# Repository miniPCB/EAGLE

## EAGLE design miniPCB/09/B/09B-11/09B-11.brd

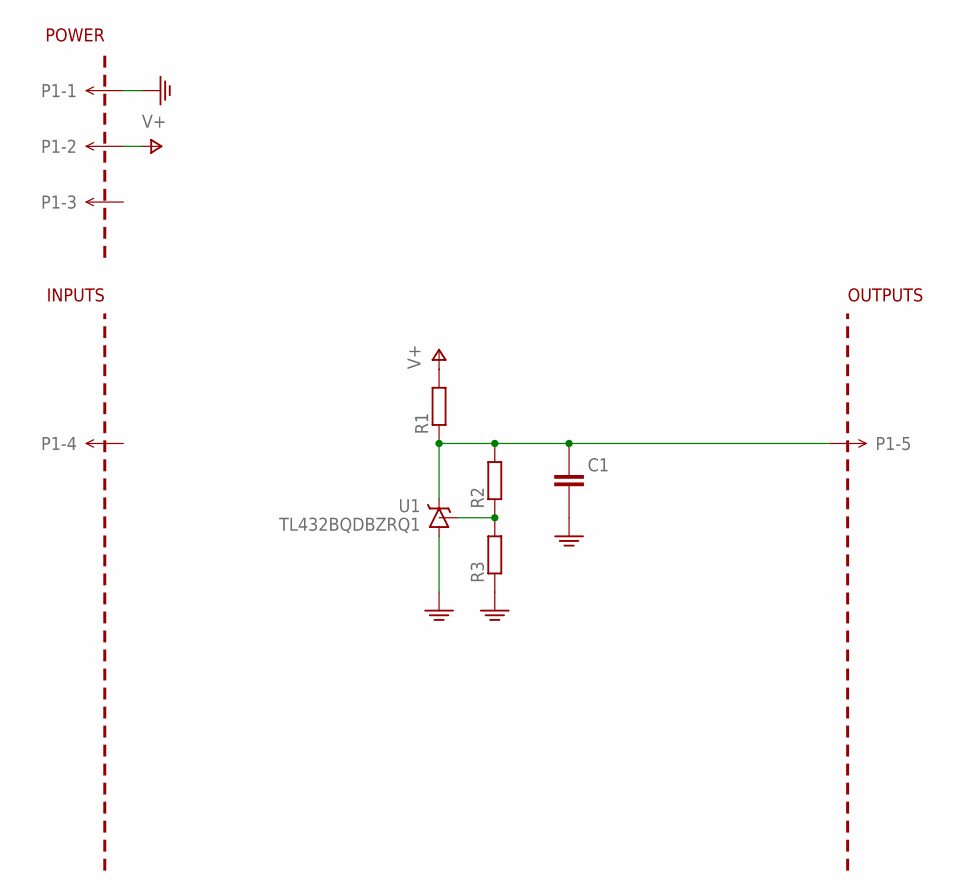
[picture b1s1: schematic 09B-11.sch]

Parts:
C1: CAPACITORSMD; C0805
P1: MINIPCB_5P5P; PINS_1X5
PCB1: MINIPCB_0PPCB20-20; PCB20-20; PART_NUMBER 09B-11
R1, R2, R3: RESISTORSMD; R0805
U1: TL432BQDBZRQ1; SOT95P237X112-3N

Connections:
GND: C1.2ASDF (-), P1.1, R3.1, U1.3 (A)
unnamed: C1.1ASD (+), P1.5, R1.1, R2.2, U1.1 (C)
unnamed: R2.1, R3.2, U1.2 (REF)
V+: P1.2, R1.2

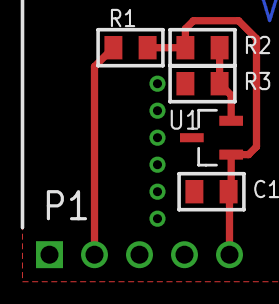
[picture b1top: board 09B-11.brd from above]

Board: 2 copper layers, 7 parts (0 on the bottom side), 4 nets.

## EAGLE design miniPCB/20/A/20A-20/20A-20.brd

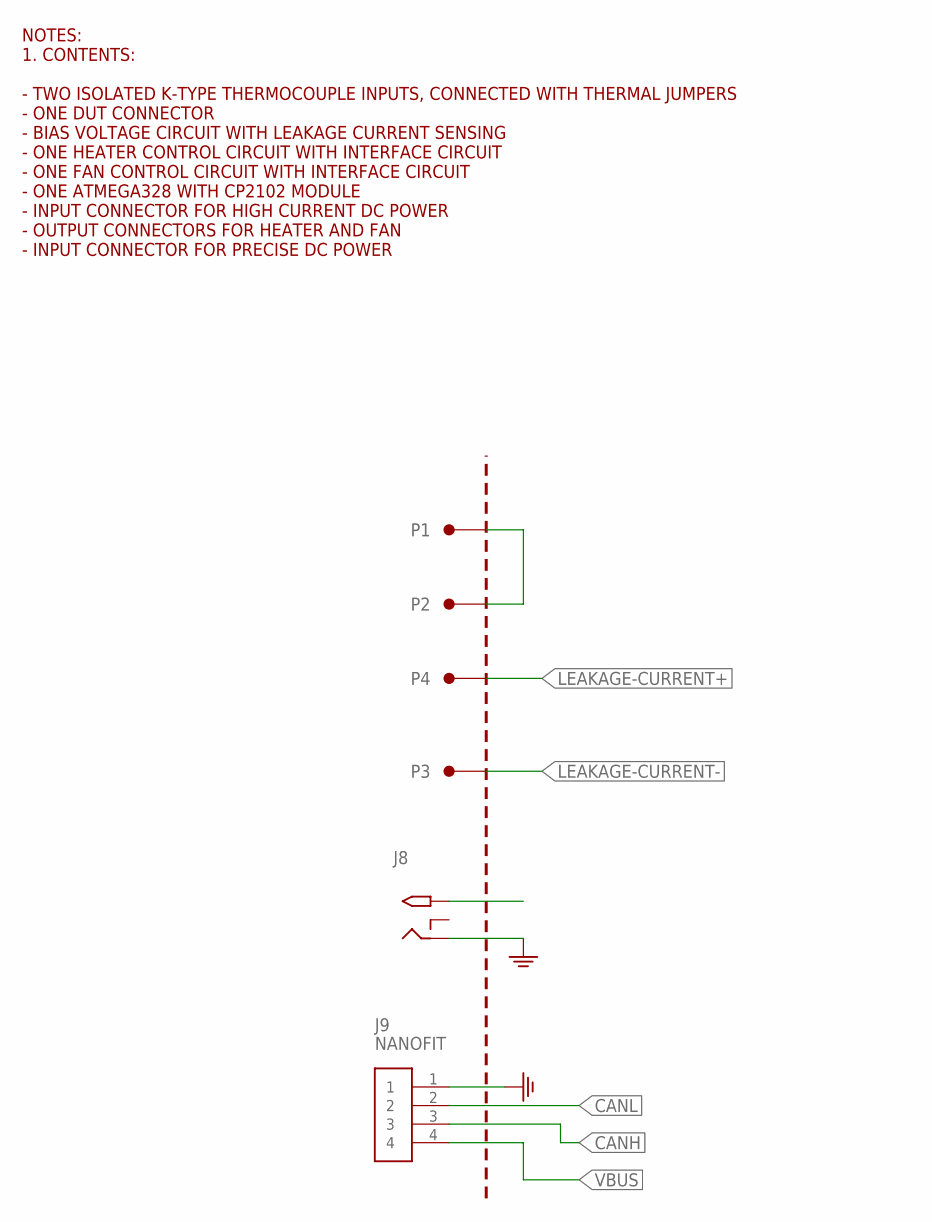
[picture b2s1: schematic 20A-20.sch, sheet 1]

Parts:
J8: 2.1MMJACKTHM; PJ-102A
J9: NANOFIT; PINS_4_NANOFIT_RA
P1, P2, P3, P4: PINS_1571-0500; BANNAN_JACK_4MM_H
PCB1: MINIPCB_0P100X100; MINIPCB_DOCK_100X100; PART_NUMBER 20A-20

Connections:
CANH: J9.3; also elsewhere on the board
CANL: J9.2; also elsewhere on the board
GND: J8.RING, J9.1; also elsewhere on the board
LEAKAGE-CURRENT+: P4.1, P4.2; also elsewhere on the board
LEAKAGE-CURRENT-: P3.1, P3.2; also elsewhere on the board
unnamed: P1.1, P1.2, P2.1, P2.2
VBUS: J9.4

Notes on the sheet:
NOTES: 1. CONTENTS: - TWO ISOLATED K-TYPE THERMOCOUPLE INPUTS, CONNECTED WITH THERMAL JUMPERS - ONE DUT CONNECTOR - BIAS VOLTAGE CIRCUIT WITH LEAKAGE CURRENT SENSING - ONE HEATER CONTROL CIRCUIT WITH INTERFACE CIRCUIT - ONE FAN CONTROL CIRCUIT WITH INTERFACE CIRCUIT - ONE ATMEGA328 WITH CP2102 MODU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

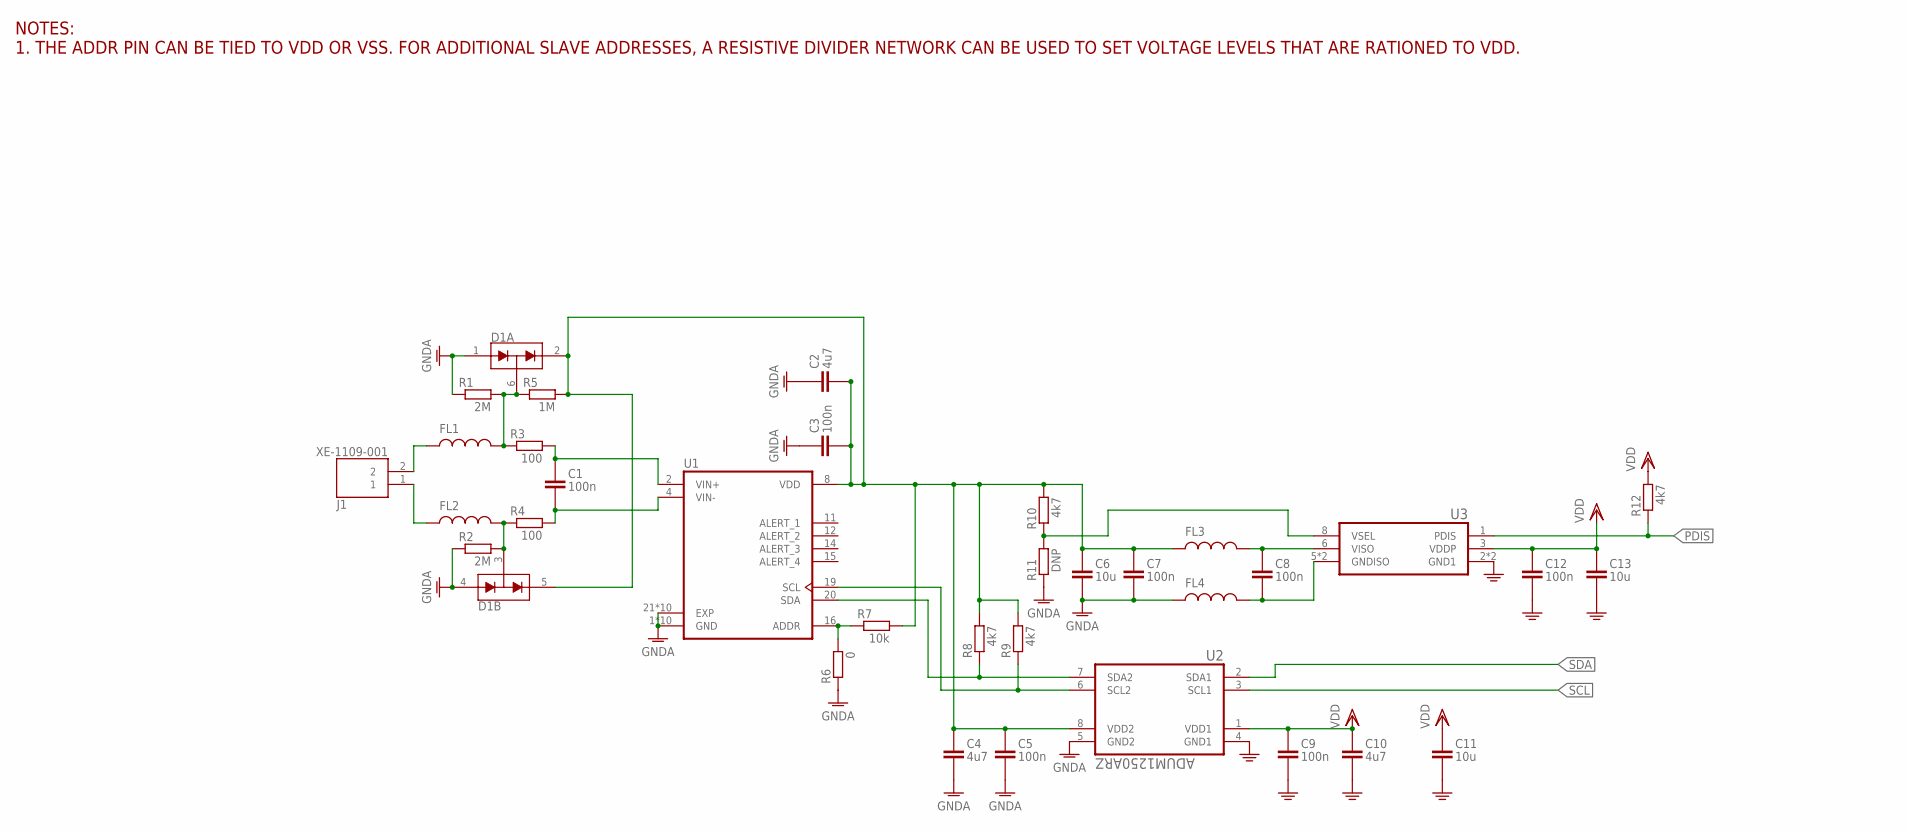
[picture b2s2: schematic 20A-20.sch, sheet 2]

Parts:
C1, C3, C5, C7, C8, C9, C12: 100n; C0402
C2, C4, C10: 4u7; C0402
C6, C11, C13: 10u; C0805
D1: SDA004-7; SOT363
FL1, FL2, FL3, FL4: BLM03HG601SZ1D; R0402
J1: XE-1109-001
R1, R2: 2M; R0402
R3, R4: 100; R0402
R5: 1M; R0402
R6: 0; R0402
R7: 10k; R0402
R8, R9, R10, R12: 4k7; R0402
R11: DNP; R0402
U1: MCP9600T-I/MX; QFN65P500X500X100-21N_MCP9600T-I/MX
U2: ADUM1250ARZ; SOIC127P600X175-8N
U3: ADUM6280; SOIC127P600X175-8N

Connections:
GND: C9.2 (-), C10.2 (-), C11.2ASDF (-), C12.2 (-), C13.2ASDF (-), U2.4 (GND1), U3.2 (GND1), U3.4 (GND1); also elsewhere on the board
GNDA: C2.1 (+), C3.1 (+), C4.2 (-), C5.2 (-), C6.2ASDF (-), C7.2 (-), D1.1 (A1), D1.4 (A1), FL4.1, R1.1, R2.1, R6.1, R11.1, U1.1 (GND), U1.3 (GND), U1.5 (GND), U1.6 (GND), U1.7 (GND), U1.9 (GND), U1.10 (GND), U1.13 (GND), U1.17 (GND), U1.18 (GND), U1.21 (EXP), U1.22 (EXP), U1.23 (EXP), U1.24 (EXP), U1.25 (EXP), U1.26 (EXP), U1.27 (EXP), U1.28 (EXP), U1.29 (EXP), U1.30 (EXP), U2.5 (GND2); also elsewhere on the board
unnamed: D1.6 (COM), FL1.2, R1.2, R3.1, R5.1
unnamed: R9.1, U1.19 (SCL), U2.6 (SCL2)
unnamed: R8.1, U1.20 (SDA), U2.7 (SDA2)
unnamed: C8.2 (-), FL4.2, U3.5 (GNDISO), U3.7 (GNDISO)
unnamed: C8.1 (+), FL3.2, U3.6 (VISO)
unnamed: R10.1, R11.2, U3.8 (VSEL)
unnamed: R6.2, R7.1, U1.16 (ADDR)
unnamed: C1.1 (+), R3.2, U1.2 (VIN+)
unnamed: D1.3 (COM), FL2.2, R2.2, R4.1
unnamed: C1.2 (-), R4.2, U1.4 (VIN-)
unnamed: FL1.1, J1.2
unnamed: FL2.1, J1.1
PDIS: R12.1, U3.1 (PDIS); also elsewhere on the board
SCL: U2.3 (SCL1); also elsewhere on the board
SDA: U2.2 (SDA1); also elsewhere on the board
VDD: C9.1 (+), C10.1 (+), C11.1ASD (+), C12.1 (+), C13.1ASD (+), R12.2, U2.1 (VDD1), U3.3 (VDDP); also elsewhere on the board
VISO: C2.2 (-), C3.2 (-), C4.1 (+), C5.1 (+), C6.1ASD (+), C7.1 (+), D1.2 (C2), D1.5 (C2), FL3.1, R5.2, R7.2, R8.2, R9.2, R10.2, U1.8 (VDD), U2.8 (VDD2)

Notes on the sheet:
NOTES: 1. THE ADDR PIN CAN BE TIED TO VDD OR VSS. FOR ADDITIONAL SLAVE ADDRESSES, A RESISTIVE DIVIDER NETWORK CAN BE USED TO SET VOLTAGE LEVELS THAT ARE RATIONED TO VDD.

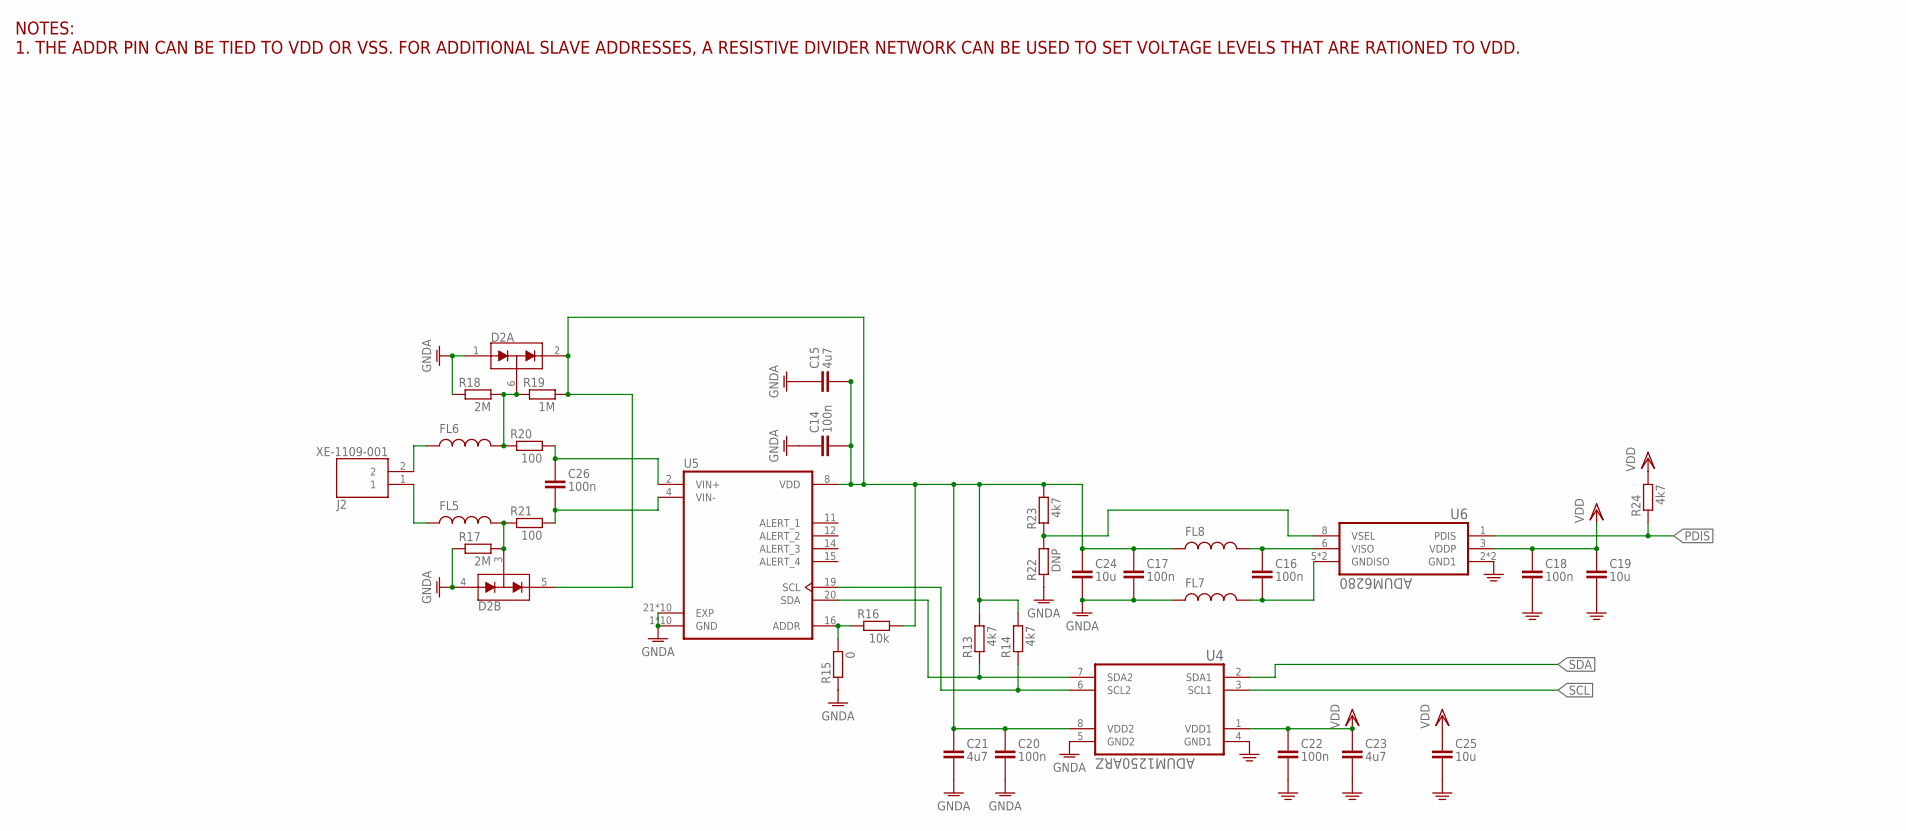
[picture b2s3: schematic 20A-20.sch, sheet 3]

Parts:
C14, C16, C17, C18, C20, C22, C26: 100n; C0402
C15, C21, C23: 4u7; C0402
C19, C24, C25: 10u; C0805
D2: SDA004-7; SOT363
FL5, FL6, FL7, FL8: BLM03HG601SZ1D; R0402
J2: XE-1109-001
R13, R14, R23, R24: 4k7; R0402
R15: 0; R0402
R16: 10k; R0402
R17, R18: 2M; R0402
R19: 1M; R0402
R20, R21: 100; R0402
R22: DNP; R0402
U4: ADUM1250ARZ; SOIC127P600X175-8N
U5: MCP9600T-I/MX; QFN65P500X500X100-21N_MCP9600T-I/MX
U6: ADUM6280; SOIC127P600X175-8N

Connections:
GND: C18.2 (-), C19.2ASDF (-), C22.2 (-), C23.2 (-), C25.2ASDF (-), U4.4 (GND1), U6.2 (GND1), U6.4 (GND1); also elsewhere on the board
GNDA: C14.1 (+), C15.1 (+), C17.2 (-), C20.2 (-), C21.2 (-), C24.2ASDF (-), D2.1 (A1), D2.4 (A1), FL7.1, R15.1, R17.1, R18.1, R22.1, U4.5 (GND2), U5.1 (GND), U5.3 (GND), U5.5 (GND), U5.6 (GND), U5.7 (GND), U5.9 (GND), U5.10 (GND), U5.13 (GND), U5.17 (GND), U5.18 (GND), U5.21 (EXP), U5.22 (EXP), U5.23 (EXP), U5.24 (EXP), U5.25 (EXP), U5.26 (EXP), U5.27 (EXP), U5.28 (EXP), U5.29 (EXP), U5.30 (EXP); also elsewhere on the board
unnamed: R14.1, U4.6 (SCL2), U5.19 (SCL)
unnamed: R13.1, U4.7 (SDA2), U5.20 (SDA)
unnamed: R15.2, R16.1, U5.16 (ADDR)
unnamed: D2.6 (COM), FL6.2, R18.2, R19.1, R20.1
unnamed: D2.3 (COM), FL5.2, R17.2, R21.1
unnamed: C26.1 (+), R20.2, U5.2 (VIN+)
unnamed: C26.2 (-), R21.2, U5.4 (VIN-)
unnamed: FL6.1, J2.2
unnamed: FL5.1, J2.1
unnamed: R22.2, R23.1, U6.8 (VSEL)
unnamed: C16.2 (-), FL7.2, U6.5 (GNDISO), U6.7 (GNDISO)
unnamed: C16.1 (+), FL8.2, U6.6 (VISO)
PDIS: R24.1, U6.1 (PDIS); also elsewhere on the board
SCL: U4.3 (SCL1); also elsewhere on the board
SDA: U4.2 (SDA1); also elsewhere on the board
VDD: C18.1 (+), C19.1ASD (+), C22.1 (+), C23.1 (+), C25.1ASD (+), R24.2, U4.1 (VDD1), U6.3 (VDDP); also elsewhere on the board
VISO1: C14.2 (-), C15.2 (-), C17.1 (+), C20.1 (+), C21.1 (+), C24.1ASD (+), D2.2 (C2), D2.5 (C2), FL8.1, R13.2, R14.2, R16.2, R19.2, R23.2, U4.8 (VDD2), U5.8 (VDD)

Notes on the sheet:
NOTES: 1. THE ADDR PIN CAN BE TIED TO VDD OR VSS. FOR ADDITIONAL SLAVE ADDRESSES, A RESISTIVE DIVIDER NETWORK CAN BE USED TO SET VOLTAGE LEVELS THAT ARE RATIONED TO VDD.

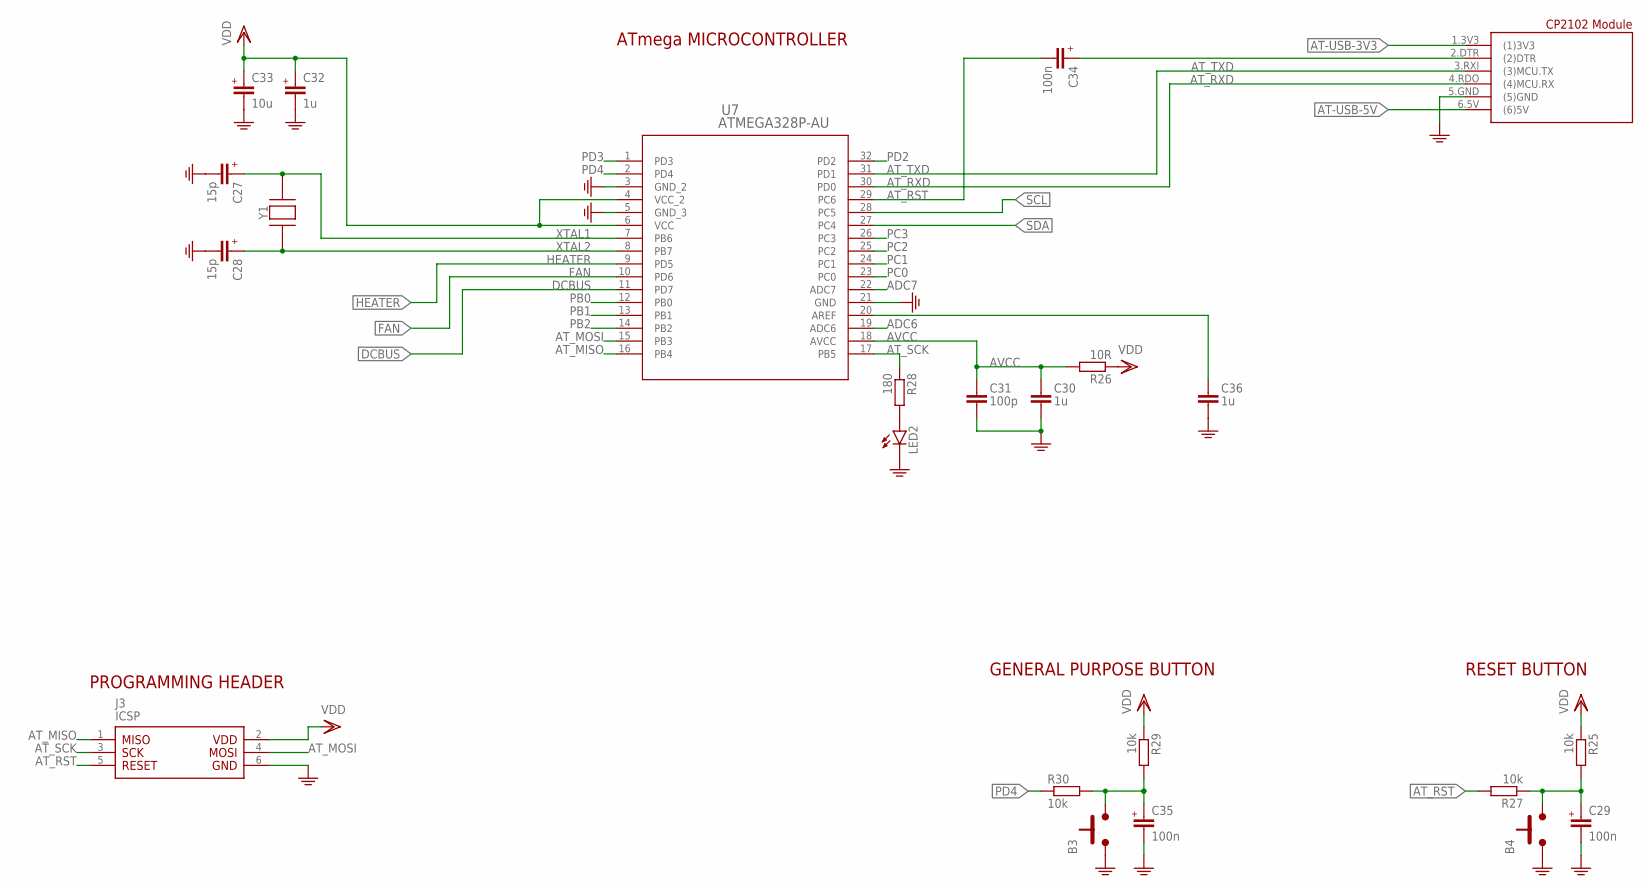
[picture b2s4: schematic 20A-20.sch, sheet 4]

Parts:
B3, B4: PUSHBUTTON6X6MM; 6X6MM
C27, C28: 15p; C0603
C29, C34, C35: 100n; C0805
C30, C32, C36: 1u; C0805
C31: 100p; C0805
C33: 10u; C0805
J3: ICSP; PINS_6-2X3_AT
LED2: LEDSML0805; SML0805
R25, R27, R29, R30: 10k; R0805
R26: 10R; R0805
R28: 180; R0805
U7: ATMEGA328P-AU; 32A_ATM
U8: VIVA_USB-TTL; VIVA_USB_TTL_SUBTEXT
Y1: CRYSTAL-3225_4P; TXC7M2

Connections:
ADC6: U7.19 (ADC6)
ADC7: U7.22 (ADC7)
AT-USB-3V3: U8.1.3V3 ((1)3V3)
AT-USB-5V: U8.6.5V ((6)5V)
AT_DTR_CAP: C34.1 (+), U8.2.DTR ((2)DTR)
AT_MISO: J3.1, U7.16 (PB4)
AT_MOSI: J3.4, U7.15 (PB3)
AT_RST: C34.2 (-), J3.5, R27.2, U7.29 (PC6)
AT_RST_CAP: B4.3.B (2), B4.4.B (2), C29.1 (+), R25.2, R27.1
AT_RXD: U7.30 (PD0), U8.4.RDO ((4)MCU.RX)
AT_SCK: J3.3, R28.1, U7.17 (PB5)
AT_TXD: U7.31 (PD1), U8.3.RXI ((3)MCU.TX)
AVCC: C30.1, C31.1, R26.2, U7.18 (AVCC)
DCBUS: U7.11 (PD7); also elsewhere on the board
FAN: U7.10 (PD6); also elsewhere on the board
GND: B3.1.A (1), B3.2.A (1), B4.1.A (1), B4.2.A (1), C27.1 (-), C28.1 (-), C29.2 (-), C30.2, C31.2, C32.2 (-), C33.2 (-), C35.2 (-), C36.2, J3.6, LED2.C, U7.3 (GND_2), U7.5 (GND_3), U7.21 (GND), U8.5.GND ((5)GND); also elsewhere on the board
HEATER: U7.9 (PD5); also elsewhere on the board
unnamed: C36.1, U7.20 (AREF)
unnamed: LED2.A, R28.2
PB0: U7.12 (PB0)
PB1: U7.13 (PB1)
PB2: U7.14 (PB2)
PC0: U7.23 (PC0)
PC1: U7.24 (PC1)
PC2: U7.25 (PC2)
PC3: U7.26 (PC3)
PD2: U7.32 (PD2)
PD3: U7.1 (PD3)
PD4: R30.1, U7.2 (PD4)
PD4-CAP: B3.3.B (2), B3.4.B (2), C35.1 (+), R29.2, R30.2
SCL: U7.28 (PC5); also elsewhere on the board
SDA: U7.27 (PC4); also elsewhere on the board
VDD: C32.1 (+), C33.1 (+), J3.2, R25.1, R26.1, R29.1, U7.4 (VCC_2), U7.6 (VCC); also elsewhere on the board
XTAL1: C27.2 (+), U7.7 (PB6), Y1.3 (2)
XTAL2: C28.2 (+), U7.8 (PB7), Y1.1

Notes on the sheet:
PROGRAMMING HEADER
ATmega MICROCONTROLLER
RESET BUTTON
GENERAL PURPOSE BUTTON

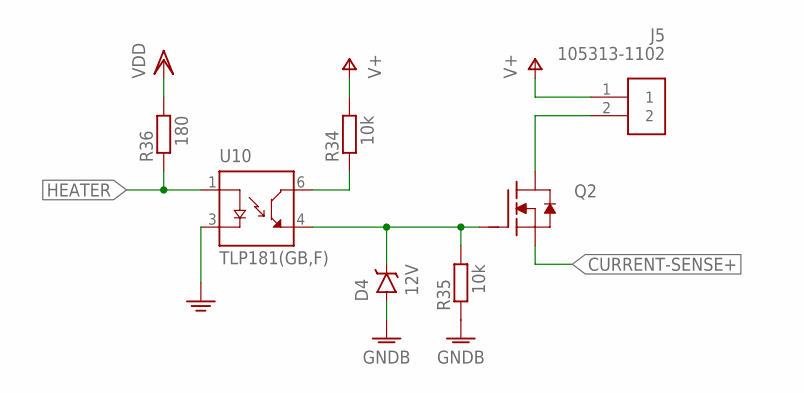
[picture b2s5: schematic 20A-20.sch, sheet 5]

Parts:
D4: 12V; SOT23
J5: 105313-1102; PINS_2-NANOFIT-H
Q2: MOSFET-NDPAK; DPACK
R34, R35: 10k; R0805
R36: 180; R0805
U10: TLP181(GB,F); SOIC254P700X280-4N

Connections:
CURRENT-SENSE+: Q2.3 (S); also elsewhere on the board
GND: U10.3 (C); also elsewhere on the board
GNDB: D4.1 (A), R35.1; also elsewhere on the board
HEATER: R36.1, U10.1 (A); also elsewhere on the board
unnamed: D4.3 (C), Q2.1 (G), R35.2, U10.4 (ET)
unnamed: J5.2, Q2.4 (D)
unnamed: R34.1, U10.6 (CT)
V+: J5.1, R34.2; also elsewhere on the board
VDD: R36.2; also elsewhere on the board

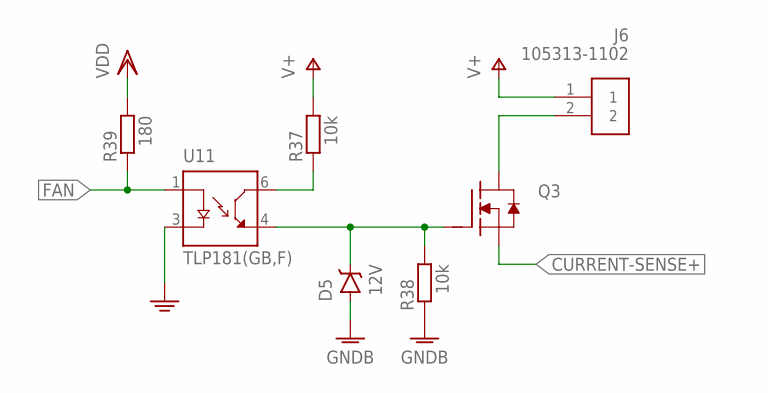
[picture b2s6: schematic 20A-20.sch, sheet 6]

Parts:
D5: 12V; SOT23
J6: 105313-1102; PINS_2-NANOFIT-H
Q3: MOSFET-NDPAK; DPACK
R37, R38: 10k; R0805
R39: 180; R0805
U11: TLP181(GB,F); SOIC254P700X280-4N

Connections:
CURRENT-SENSE+: Q3.3 (S); also elsewhere on the board
FAN: R39.1, U11.1 (A); also elsewhere on the board
GND: U11.3 (C); also elsewhere on the board
GNDB: D5.1 (A), R38.1; also elsewhere on the board
unnamed: D5.3 (C), Q3.1 (G), R38.2, U11.4 (ET)
unnamed: J6.2, Q3.4 (D)
unnamed: R37.1, U11.6 (CT)
V+: J6.1, R37.2; also elsewhere on the board
VDD: R39.2; also elsewhere on the board

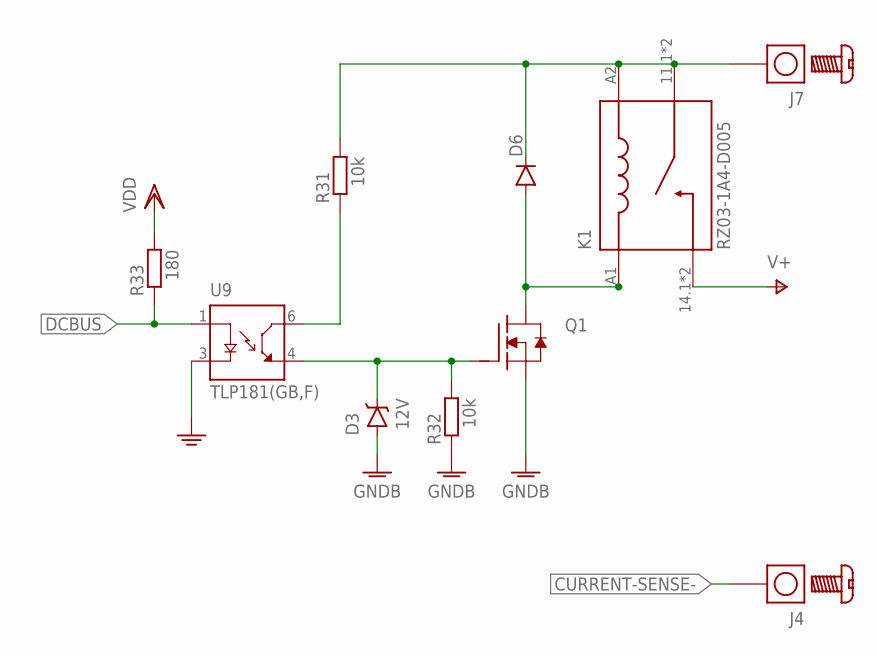
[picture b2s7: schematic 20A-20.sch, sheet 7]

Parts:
D3: 12V; SOT23
D6: DIODE-SOD323-W; SOD323-W
J4, J7: SCREW-TERMINAL; SCREW-TERMINAL-M3
K1: RZ03-1A4-D005; RELAY_RZ03-1A4-D005
Q1: MOSFET-NSOT23; SOT23
R31, R32: 10k; R0805
R33: 180; R0805
U9: TLP181(GB,F); SOIC254P700X280-4N

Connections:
CURRENT-SENSE-: J4.1, J4.2, J4.3, J4.4; also elsewhere on the board
DCBUS: R33.1, U9.1 (A); also elsewhere on the board
GND: U9.3 (C); also elsewhere on the board
GNDB: D3.1 (A), Q1.2 (S), R32.1; also elsewhere on the board
unnamed: D3.3 (C), Q1.1 (G), R32.2, U9.4 (ET)
unnamed: D6.C, J7.1, J7.2, J7.3, J7.4, K1.11.1 (11), K1.11.2 (11), K1.A2, R31.2
unnamed: D6.A, K1.A1, Q1.3 (D)
unnamed: R31.1, U9.6 (CT)
V+: K1.14.1 (14), K1.14.2 (14); also elsewhere on the board
VDD: R33.2; also elsewhere on the board

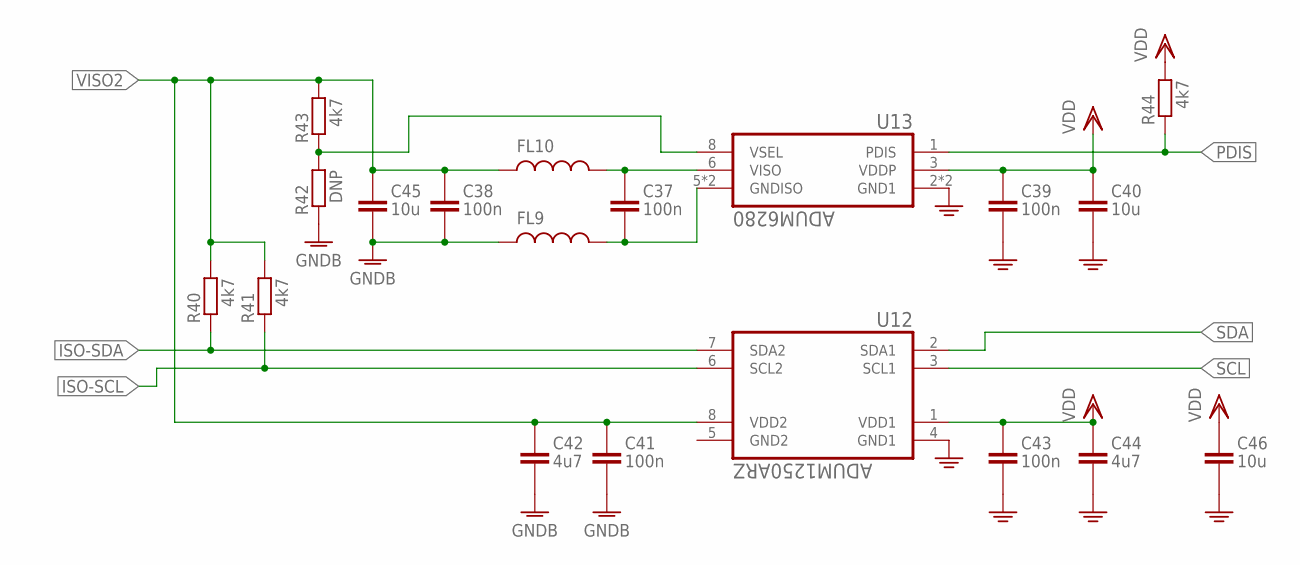
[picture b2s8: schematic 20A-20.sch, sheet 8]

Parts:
C37, C38, C39, C41, C43: 100n; C0402
C40, C45, C46: 10u; C0805
C42, C44: 4u7; C0402
FL9, FL10: BLM03HG601SZ1D; R0402
R40, R41, R43, R44: 4k7; R0402
R42: DNP; R0402
U12: ADUM1250ARZ; SOIC127P600X175-8N
U13: ADUM6280; SOIC127P600X175-8N

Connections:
GND: C39.2 (-), C40.2ASDF (-), C43.2 (-), C44.2 (-), C46.2ASDF (-), U12.4 (GND1), U13.2 (GND1), U13.4 (GND1); also elsewhere on the board
GNDB: C38.2 (-), C41.2 (-), C42.2 (-), C45.2ASDF (-), FL9.1, R42.1; also elsewhere on the board
ISO-SCL: R41.1, U12.6 (SCL2); also elsewhere on the board
ISO-SDA: R40.1, U12.7 (SDA2); also elsewhere on the board
unnamed: R42.2, R43.1, U13.8 (VSEL)
unnamed: C37.2 (-), FL9.2, U13.5 (GNDISO), U13.7 (GNDISO)
unnamed: C37.1 (+), FL10.2, U13.6 (VISO)
PDIS: R44.1, U13.1 (PDIS); also elsewhere on the board
SCL: U12.3 (SCL1); also elsewhere on the board
SDA: U12.2 (SDA1); also elsewhere on the board
VDD: C39.1 (+), C40.1ASD (+), C43.1 (+), C44.1 (+), C46.1ASD (+), R44.2, U12.1 (VDD1), U13.3 (VDDP); also elsewhere on the board
VISO2: C38.1 (+), C41.1 (+), C42.1 (+), C45.1ASD (+), FL10.1, R40.2, R41.2, R43.2, U12.8 (VDD2); also elsewhere on the board

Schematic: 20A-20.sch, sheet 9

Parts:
C47: 470p; C0402
C48, C51: 100n; C0402
C49, C50: 4u7; C0402
R45: WSL2010R5000DEA; R5025
R46: 22; R0402
R47, R48: DNP; R0402
U14: ADC121C027CIMK; SOT23-6
U15: INA181; SOT23-6

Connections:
CURRENT-SENSE+: R45.2, U15.3 (3.IN+); also elsewhere on the board
CURRENT-SENSE-: R45.1, U15.4 (4.IN-); also elsewhere on the board
GNDB: C47.2 (-), C48.2 (-), C49.2 (-), C50.2 (-), C51.2 (-), R48.2, U14.2 (2.GND), U15.2 (2.GND), U15.5 (5.REF); also elsewhere on the board
ISO-SCL: U14.5 (5.SCL); also elsewhere on the board
ISO-SDA: U14.6 (6.SDA); also elsewhere on the board
unnamed: C47.1 (+), R46.2, U14.3 (3.VIN)
unnamed: R46.1, U15.1 (1.OUT)
unnamed: R47.1, R48.1, U14.4 (4.ADDR)
VISO2: C48.1 (+), C49.1 (+), C50.1 (+), C51.1 (+), R47.2, U14.1 (1.VA), U15.6 (6.VS); also elsewhere on the board

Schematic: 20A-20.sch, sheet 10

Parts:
C52: 470p; C0402
C53, C56: 100n; C0402
C54, C55: 4u7; C0402
R49: WSL2010R5000DEA; R5025
R50: 22; R0402
R51, R52: DNP; R0402
U16: ADC121C027CIMK; SOT23-6
U17: INA181; SOT23-6

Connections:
GND: C52.2 (-), C53.2 (-), C54.2 (-), C55.2 (-), C56.2 (-), R52.2, U16.2 (2.GND), U17.2 (2.GND), U17.5 (5.REF); also elsewhere on the board
LEAKAGE-CURRENT+: R49.2, U17.3 (3.IN+); also elsewhere on the board
LEAKAGE-CURRENT-: R49.1, U17.4 (4.IN-); also elsewhere on the board
unnamed: C52.1 (+), R50.2, U16.3 (3.VIN)
unnamed: R50.1, U17.1 (1.OUT)
unnamed: R51.1, R52.1, U16.4 (4.ADDR)
SCL: U16.5 (5.SCL); also elsewhere on the board
SDA: U16.6 (6.SDA); also elsewhere on the board
VDD: C53.1 (+), C54.1 (+), C55.1 (+), C56.1 (+), R51.2, U16.1 (1.VA), U17.6 (6.VS); also elsewhere on the board

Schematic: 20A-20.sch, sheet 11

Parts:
C57: 4n7; C0402
C58: 100n; C0402
C59: 4u7; C0402
R53, R54: 60; R0402
R55: 300; R0402
U18: MCP2561FD-E/MF; SON65P300X300X100-9N

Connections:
CAN-RX: U18.4 (RX)
CAN-STBY: U18.8 (STBY)
CAN-TX: U18.1 (TX)
CANH: R54.2, U18.7 (CANH); also elsewhere on the board
CANL: R53.2, U18.6 (CANL); also elsewhere on the board
GND: C57.2 (-), C58.2 (-), C59.2 (-), U18.2 (VSS), U18.9 (VSS); also elsewhere on the board
unnamed: R55.1, U18.5 (SPLIT)
unnamed: C57.1 (+), R53.1, R54.1, R55.2
VDD: C58.1 (+), C59.1 (+), U18.3 (VDD); also elsewhere on the board

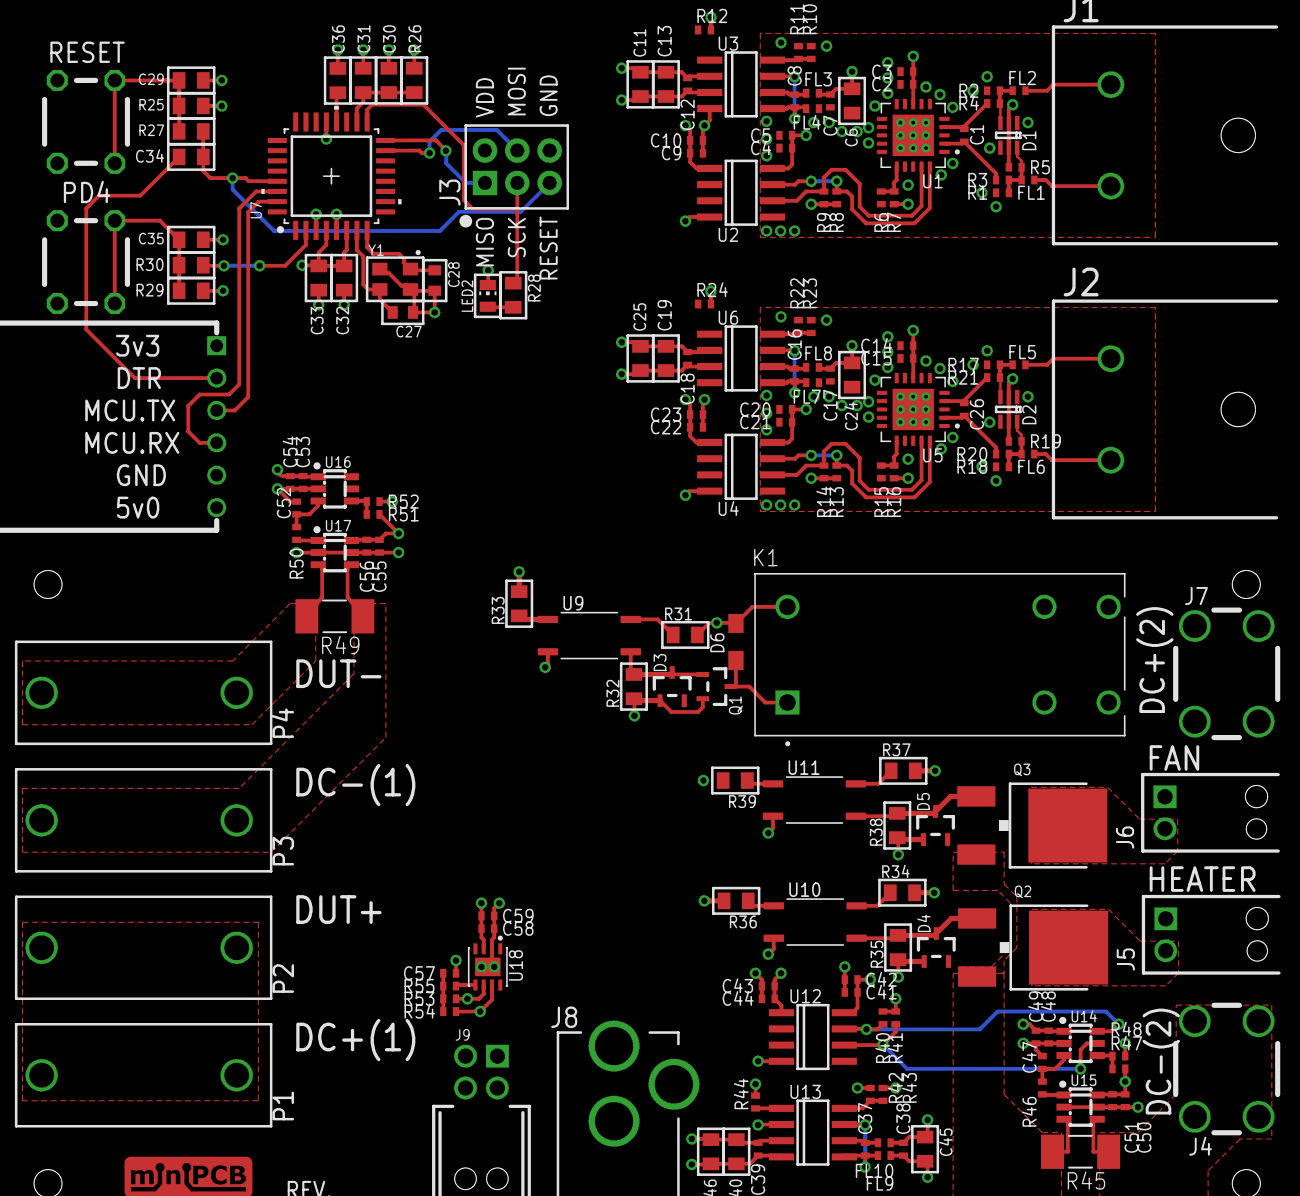
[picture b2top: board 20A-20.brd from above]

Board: 4 copper layers, 170 parts (0 on the bottom side), 83 nets.

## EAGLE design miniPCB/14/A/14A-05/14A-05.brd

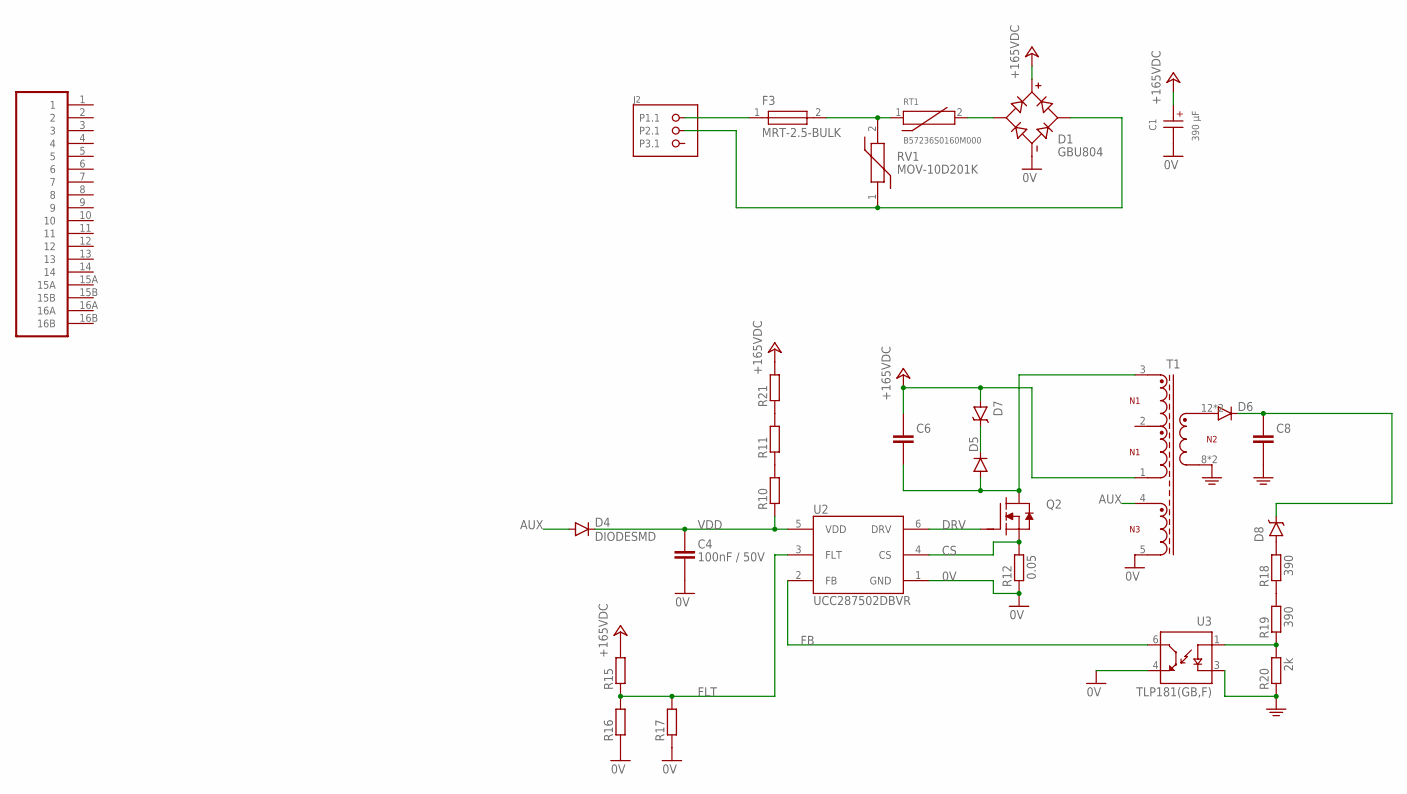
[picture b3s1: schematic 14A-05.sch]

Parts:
C1: 390 µF; WCAP-AIE8_30X45(DXL)
C4: 100nF / 50V; C0805
C6: CAPACITORSMD; C0805
C8: CAPACITOR3.5MM; C3-5MM
D1: GBU804; SIP343W114P508L2205H2134Q4
D4, D5, D6: DIODESMD; DO214AC
D7, D8: ZENERSOD80C; SOD80C
F3: MRT-2.5-BULK; FUSE_MRT-2.5-BULK
J1: BC_HOUSING_107.6MM; BC_HOUSING_107MM
J2: 2604-3103; P-2604-3103
Q2: MOSFET-NDPAK; DPACK
R10, R11, R15, R16, R17, R21: RESISTORSMD; R0805
R12: 0.05; R2512K
R18, R19: 390; R0805
R20: 2k; R0805
RT1: B57236S0160M000; THRMRB500W60L1150T500H1600
RV1: MOV-10D201K; MOV10D201KTR
T1: TRANSFORMER-FLYBACK; 750342415
U2: UCC287502DBVR; SOT23-6
U3: TLP181(GB,F); SOIC254P700X280-4N

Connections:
0V: C1.2 (-), C4.2ASDF (-), D1.-, R12.1, R16.1, R17.1, T1.5, U2.1 (GND), U3.4 (ET)
+24V: C1.1 (+), C6.1ASD (+), D1.+, D7.A, R15.2, R21.2, T1.1
AUX: D4.A, T1.4
CS: Q2.3 (S), R12.2, U2.4 (CS)
DRV: Q2.1 (G), U2.6 (DRV)
FB: U2.2 (FB), U3.6 (CT)
FLT: R15.1, R16.2, R17.2, U2.3 (FLT)
GND: C8.-, R20.1, T1.8 (8,9), T1.9 (8,9), U3.3 (C)
unnamed: F3.2, RT1.1, RV1.2
unnamed: D1.AC1, J2.P2.1, J2.P2.2 (P2.1), RV1.1
unnamed: D1.AC2, RT1.2
unnamed: F3.1, J2.P1.1, J2.P1.2 (P1.1)
unnamed: R10.2, R11.1
unnamed: C6.2ASDF (-), D5.A, Q2.4 (D), T1.3
unnamed: R19.1, R20.2, U3.1 (A)
unnamed: D6.A, T1.12 (12,13), T1.13 (12,13)
unnamed: R18.1, R19.2
unnamed: D8.A, R18.2
unnamed: D5.C, D7.C
unnamed: C8.+, D6.C, D8.C
unnamed: R11.2, R21.1
VDD: C4.1ASD (+), D4.C, R10.1, U2.5 (VDD)

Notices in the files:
parts and their libraries:
Eagle_WCAP-AIE8: Copyright: Würth Elektronik
COPYRIGHT: Copyright (C) 2021 Ultra Librarian. All rights reserved.
